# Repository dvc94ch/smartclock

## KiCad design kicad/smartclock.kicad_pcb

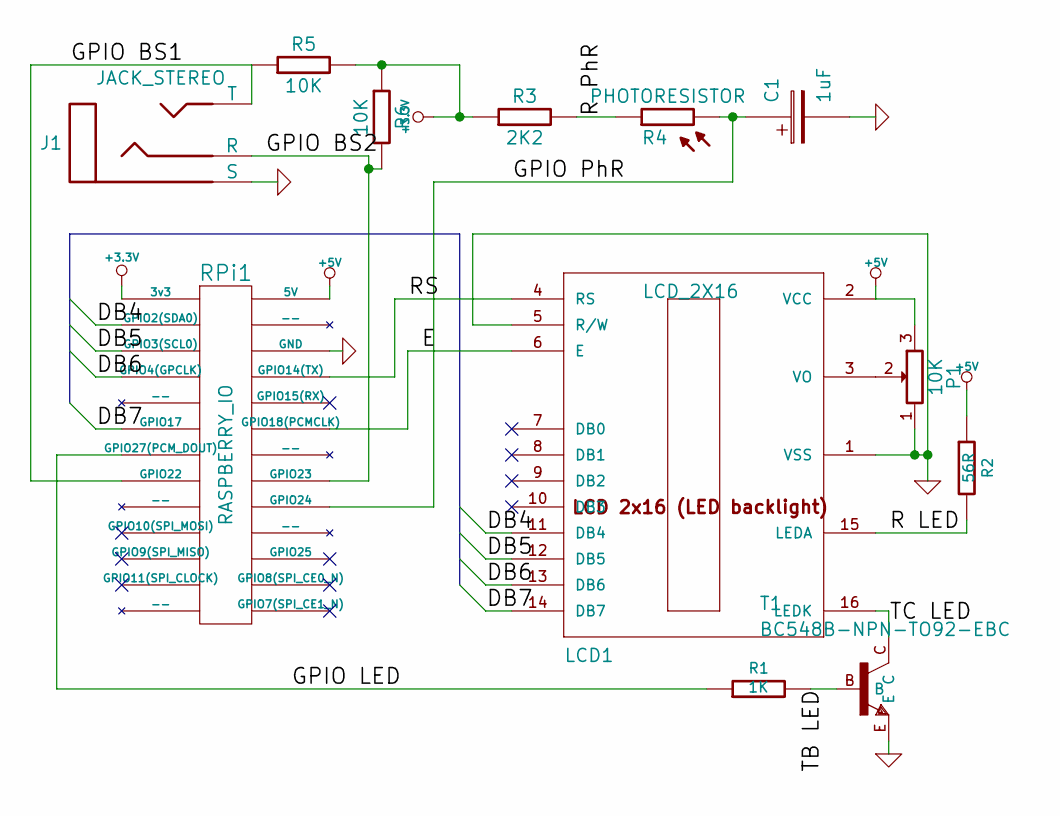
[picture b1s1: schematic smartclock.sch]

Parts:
C1: 1uF
J1: JACK_STEREO
LCD1: LCD_2X16; lcd_2x16_led_backlight-HY-1602F
P1: 10K
R1: 1K
R2: 56R
R3: 2K2
R4: PHOTORESISTOR
R5, R6: 10K
RPi1: RASPBERRY_IO
T1: BC548B-NPN-TO92-EBC; transistor-TO92-EBC

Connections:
+3.3V: R3.1, R5.2, R6.1, RPi1.1 (3v3)
+5V: LCD1.2 (VCC), P1.3, R2.1, RPi1.2 (5V)
/DB4: LCD1.11 (DB4), RPi1.3 (GPIO2(SDA0))
/DB5: LCD1.12 (DB5), RPi1.5 (GPIO3(SCL0))
/DB6: LCD1.13 (DB6), RPi1.7 (GPIO4(GPCLK))
/DB7: LCD1.14 (DB7), RPi1.11 (GPIO17)
/E: LCD1.6 (E), RPi1.12 (GPIO18(PCMCLK))
/GPIO BS1: J1.T, R5.1, RPi1.15 (GPIO22)
/GPIO BS2: J1.R, R6.2, RPi1.16 (GPIO23)
/GPIO LED: R1.1, RPi1.13 (GPIO27(PCM_DOUT))
/GPIO PhR: C1.1, R4.2, RPi1.18 (GPIO24)
/R LED: LCD1.15 (LEDA), R2.2
/R PhR: R3.2, R4.1
/RS: LCD1.4 (RS), RPi1.8 (GPIO14(TX))
/TB LED: R1.2, T1.B
/TC LED: LCD1.16 (LEDK), T1.C
GND: C1.2, J1.S, LCD1.1 (VSS), LCD1.5 (R/W), P1.1, RPi1.6 (GND), T1.E
unnamed: LCD1.3 (VO), P1.2

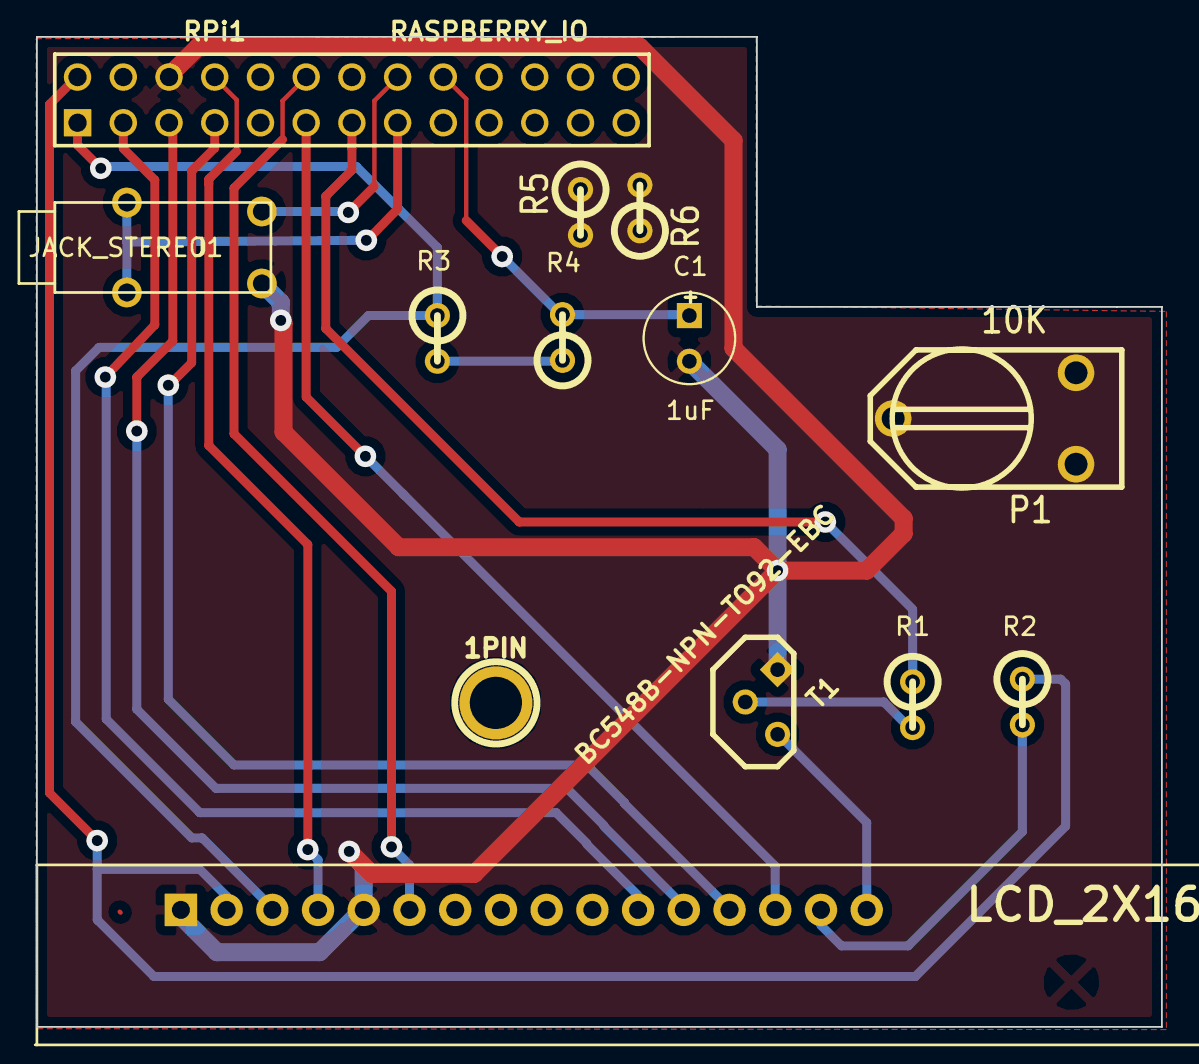
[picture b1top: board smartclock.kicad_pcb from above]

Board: 2 copper layers, 62.5 x 55.0 mm, 13 parts (0 on the bottom side), 18 nets.

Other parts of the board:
1PIN: P***; 1pin

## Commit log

2013-08-24 fixed setup, changed default setting in hue_plugin, and fixed loading default settings every time.
2013-08-25 fixing ü on lcd
2013-08-27 Added external geocoding and walking time calculations for more accurate departure time calculation.
2013-08-27 refractored main and added alarm_manager.
2013-08-27 disabled automatically switching lights on for now.
2013-08-27 added test for parsing travelmode
2013-08-27 fixed TravelTimePluginTestCase
2013-08-27 removed unused stmts in WeatherPluginTestCase
2013-08-29 fixed transport and traveltime testcases, improved algorithms, added documentation.
2013-08-29 updated readme and description.
2013-08-29 refractored transportopendata_plugin, added v as a valid variable name to pylint.
